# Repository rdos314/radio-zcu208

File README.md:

<h3>Source tree</h3>
vivado - Vivado Verilog source<br>
vitis - Vitis platform and control software<br>
linux - Peta-linux source<br>

<h3>PetaLinux build</h3>
Ubuntu 22.04.5 must be used to build PetaLinux. Link: https://releases.ubuntu.com/jammy/<br><br>

Create a user "ubuntu" since full paths are used in the source.

Install the required software modules before installing PetaLinux:<br>
sudo apt-get install iproute2 gawk python3 python build-essential gcc git make net-tools libncurses5-dev tftpd zlib1g-dev libssl-dev flex bison libselinux1 gnupg wget git-core diffstat chrpath socat xterm autoconf libtool tar unzip texinfo<br><br>

The PetaLinux installer can be downloaded here: https://www.xilinx.com/support/download/index.html/content/xilinx/en/downloadNav/embedded-design-tools.html<br>
Download the "PetaLinux installer" and the "ZCU208 BSP" to /home/ubuntu<br><br>

Install PetaLinux like this:<br>
chmod 755 ./petalinux-v2025.1-final-installer.run<br>
./petalinux-v2025.1-final-installer.run --dir /home/ubuntu/petalinux --platform "arm aarch64"<br>

Source PetaLinux before running commands:<br>
source /home/ubuntu/petalinux/settings.sh<br><br>

Create the project:<br>
mkdir radio-zcu208<br>
cd radio-zcu208<br><br>

petalinux-create -t project -s zcu208-v2025.1.bsp -n linux<br>
cd linux<br><br>

petalinux-config --get-hw-description ../platform/export/platform/hw/sdt<br><br>

Subsystem Hardware Settings -→ Memory settings -→ Set Memory size to 0x70000000<br>
Subsystem Hardware Settings -→ Ethernet settings -→ Disable obtain IP address automatically<br>
Subsystem Hardware Settings -→ Ethernet settings -→ Set Static IP address to 192.168.1.90<br>
Subsystem Hardware Settings -→ Ethernet settings -→ Set Static IP gateway to 192.168.1.1<br>
Image Packaging Configuration  -→  Set Root file system type to EXT4 (SD/eMMC/SATA/USB)<br>

Exit menuconfig and save configuration settings.<br><br>

petalinux-config -c rootfs.<br>

Filesystem Packages -→ console -→ network -→ OpenSSH -→ set openssh-sftp-server to enabled<br>
Filesystem Packages -→ misc -→ set tcf-agent to enabled<br>
Filesystem Packages -→ misc -→ set apache2 to enabled<br><br>

Exit menuconfig and save configuration settings.<br><br>

petalinux-build<br>
petalinux-package boot --uboot --force<br>
petalinux-build --sdk<br>
petalinux-package sysroot<br><br>

Copy linux/images/linux/b31.bin to project roo<br>
Copy linux/images/linux/system.dtb to project root<br>
Copy linux/images/linux/u-boot.elf to project root<br>
Copy linux/images/linux/sdk/sysroots/cortexa72-cotexa53-amd-linux/usr/include to project platform/usr/include<br>
Copy linux/images/linux/sdk/sysroots/cortexa72-cotexa53-amd-linux/usr/lib to project platform/usr/lib<br><br>

cp linux/images/linux/image.ub /media/ubuntu/boot<br>
cp linux/images/linux/boot.scr /media/ubuntu/boot<br>
sudo dd if=linux/images/linux/rootfs.ext4 of=/dev/sdb2<br><br>

<h3>Embedded Vitis</h3>

Embedded Vitis and Vivado can be installed either on Windows or on Linux. Link: https://www.xilinx.com/support/download/index.html/content/xilinx/en/downloadNav/vitis.html<br><br>

For Linux, download and install to /home/user/xilinx and then install the libs like this:<br>
cd /home/user/xilinx/2025.1/Vitis/scripts<br>
sudo ./installLibs.sh<br><br>

<h3>XRT and ZOCL</h3>

https://adaptivesupport.amd.com/s/article/1138667?language=en_US

<h3>Antennas and preamplifiers</h3>

Isolator: https://www.herostechnology.co.uk/pages/RF_Galvanic_Isolators.html                            3 MHz - 2.5 GHz<br>
LNA: https://www.pasternack.com/1.5-db-1.3-ghz-low-noise-amplifier-35-db-gain-sma-pe15a1054-p.aspx      10MHz - 1.3GHz, 35dB, 1.5 NF<br>
LNA: https://www.pasternack.com/1.7-db-550-mhz-low-noise-amplifier-29.7-db-gain-sma-pe15a1044-p.aspx    10MHz - 550 MHz, 30dB, 1.7 NF<br><br>

<h3>Example design</h3>

doc: https://docs.amd.com/r/en-US/ug1309-rf-data-converter-interface<br>
source: https://account.amd.com/en/forms/downloads/design-license-xef.html?filename=RF_Analyzer_2024_2.zip<br><br>

doc: https://www.xilinx.com/publications/products/board-kits/zcu208-dds-ila-2020p2.pdf<br>
source: https://account.amd.com/en/forms/downloads/design-license-xef.html?filename=ZCU208_dds_ila_2020p2.zip<br>

<h3>Important links</h3>
https://www.amd.com/en/products/adaptive-socs-and-fpgas/evaluation-boards/zcu208.html<br>
https://xilinx-wiki.atlassian.net/wiki/spaces/A/pages/18841823/Booting+via+Serial+ATA+SATA+on+ZCU102+Evaluation+Platform<br>
https://adaptivesupport.amd.com/s/article/000037805?language=en_US<br>
https://xilinx-wiki.atlassian.net/wiki/spaces/A/pages/18842475/PetaLinux+Yocto+Tips#PetaLinuxYoctoTips-HowtoAutoRunApplicationatStartup<br>
https://docs.amd.com/r/en-US/Vitis-Tutorials-Embedded-Software<br>
https://docs.amd.com/r/en-US/ug1209-embedded-design-tutorial/Tutorial-Design-Files<br>
https://numato.com/kb/styx-partitioning-sd-card-for-petalinux/<br>
https://adaptivesupport.amd.com/s/article/1192842?language=en_US<br>
https://github.com/Xilinx/embeddedsw/blob/master/XilinxProcessorIPLib/drivers/rfdc/examples/xrfdc_mts_example.c<br>
https://docs.amd.com/r/en-US/pg269-rf-data-converter/MTS-Sequencing<br>
https://docs.amd.com/r/en-US/ug835-vivado-tcl-commands/<br>
https://github.com/Xilinx/embeddedsw/tree/master/XilinxProcessorIPLib/drivers/board_common/src/rfclk<br>
https://layers.openembedded.org/layerindex/branch/master/layers/<br>
https://www.analog.com/en/products/adl5569.html<br>
https://ez.analog.com/rf/f/q-a/115814/adl5569-single-ended-input<br>

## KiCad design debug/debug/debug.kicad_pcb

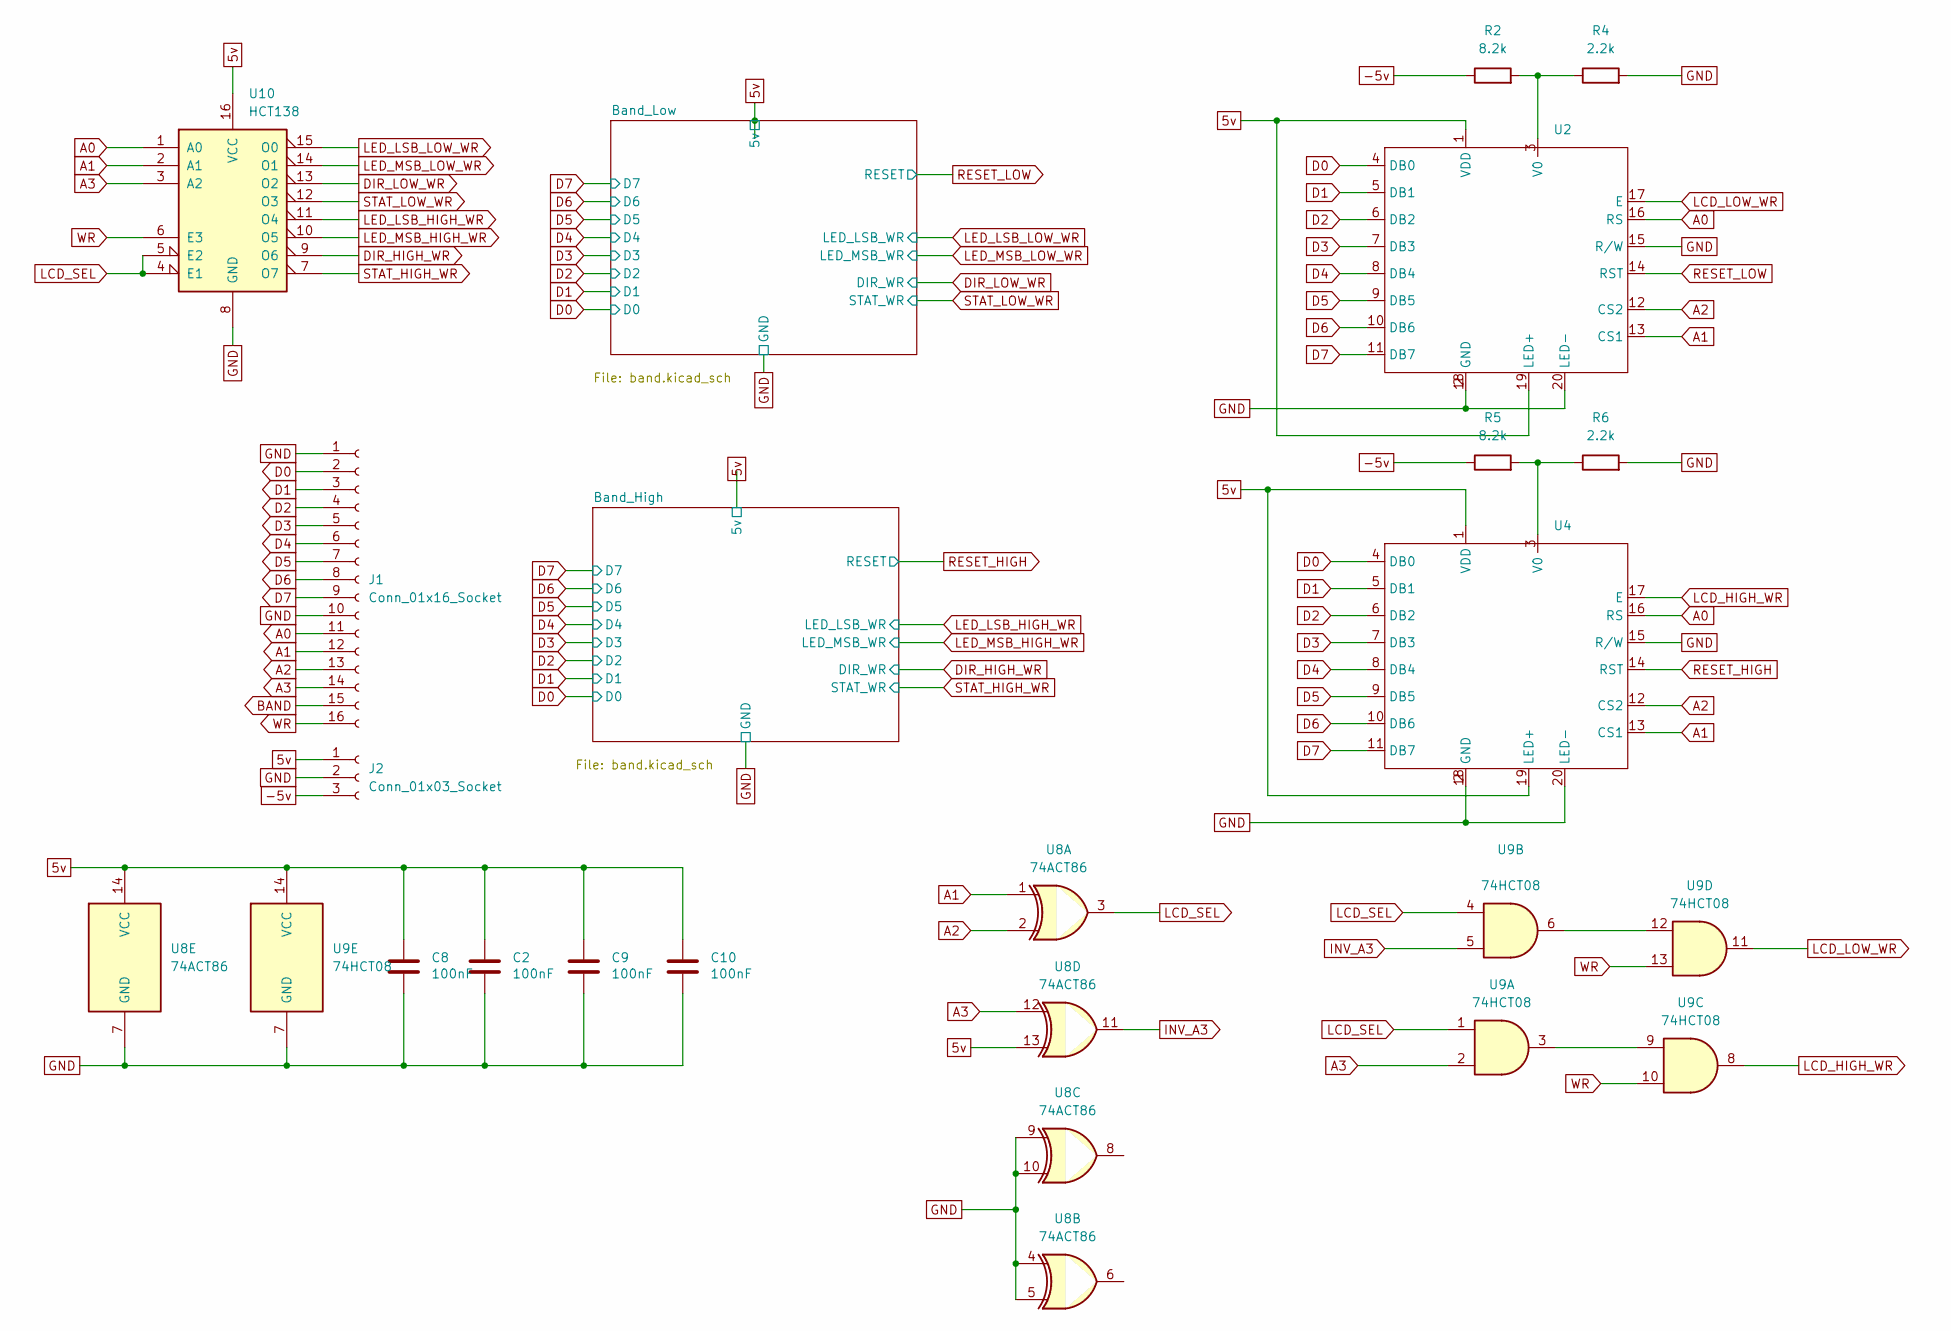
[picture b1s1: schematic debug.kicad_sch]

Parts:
C2, C8, C9, C10: 100nF; C_0805_2012Metric_Pad1.18x1.45mm_HandSolder
J1: Conn_01x16_Socket; PinSocket_1x16_P2.54mm_Vertical
J2: Conn_01x03_Socket; PinHeader_1x03_P2.54mm_Vertical
R2, R5: 8.2k; R_0805_2012Metric_Pad1.20x1.40mm_HandSolder
R4, R6: 2.2k; R_0805_2012Metric_Pad1.20x1.40mm_HandSolder
U2, U4: LCD
U8: 74ACT86; SOIC-14_3.9x8.7mm_P1.27mm
U9: 74HCT08; SOIC-14_3.9x8.7mm_P1.27mm
U10: HCT138; SOIC-16_3.9x9.9mm_P1.27mm

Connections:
5v: C2.1, C8.1, C9.1, C10.1, J2.1, U2.1 (VDD), U2.19 (LED+), U4.1 (VDD), U4.19 (LED+), U8.13, U8.14 (VCC), U9.14 (VCC), U10.16 (VCC); also elsewhere on the board
-5v: J2.3, R2.1, R5.1
A0: J1.11, U2.16 (RS), U4.16 (RS), U10.1 (A0)
A1: J1.12, U2.13 (CS1), U4.13 (CS1), U8.1, U10.2 (A1)
A2: J1.13, U2.12 (CS2), U4.12 (CS2), U8.2
A3: J1.14, U8.12, U9.2, U10.3 (A2)
BAND: J1.15
D0: J1.2, U2.4 (DB0), U4.4 (DB0); also elsewhere on the board
D1: J1.3, U2.5 (DB1), U4.5 (DB1); also elsewhere on the board
D2: J1.4, U2.6 (DB2), U4.6 (DB2); also elsewhere on the board
D3: J1.5, U2.7 (DB3), U4.7 (DB3); also elsewhere on the board
D4: J1.6, U2.8 (DB4), U4.8 (DB4); also elsewhere on the board
D5: J1.7, U2.9 (DB5), U4.9 (DB5); also elsewhere on the board
D6: J1.8, U2.10 (DB6), U4.10 (DB6); also elsewhere on the board
D7: J1.9, U2.11 (DB7), U4.11 (DB7); also elsewhere on the board
DIR_HIGH_WR: U10.9 (O6); also elsewhere on the board
DIR_LOW_WR: U10.13 (O2); also elsewhere on the board
GND: C2.2, C8.2, C9.2, C10.2, J1.1, J1.10, J2.2, R4.2, R6.2, U2.2 (GND), U2.15 (R/W), U2.18 (GND), U2.20 (LED-), U4.2 (GND), U4.15 (R/W), U4.18 (GND), U4.20 (LED-), U8.4, U8.5, U8.7 (GND), U8.9, U8.10, U9.7 (GND), U10.8 (GND); also elsewhere on the board
INV_A3: U8.11, U9.5
LCD_HIGH_WR: U4.17 (E), U9.8
LCD_LOW_WR: U2.17 (E), U9.11
LCD_SEL: U8.3, U9.1, U9.4, U10.4 (E1), U10.5 (E2)
LED_LSB_HIGH_WR: U10.11 (O4); also elsewhere on the board
LED_LSB_LOW_WR: U10.15 (O0); also elsewhere on the board
LED_MSB_HIGH_WR: U10.10 (O5); also elsewhere on the board
LED_MSB_LOW_WR: U10.14 (O1); also elsewhere on the board
unnamed: R2.2, R4.1, U2.3 (V0)
unnamed: R5.2, R6.1, U4.3 (V0)
unnamed: U9.3, U9.9
unnamed: U9.6, U9.12
RESET_HIGH: U4.14 (RST); also elsewhere on the board
RESET_LOW: U2.14 (RST); also elsewhere on the board
STAT_HIGH_WR: U10.7 (O7); also elsewhere on the board
STAT_LOW_WR: U10.12 (O3); also elsewhere on the board
WR: J1.16, U9.10, U9.13, U10.6 (E3)

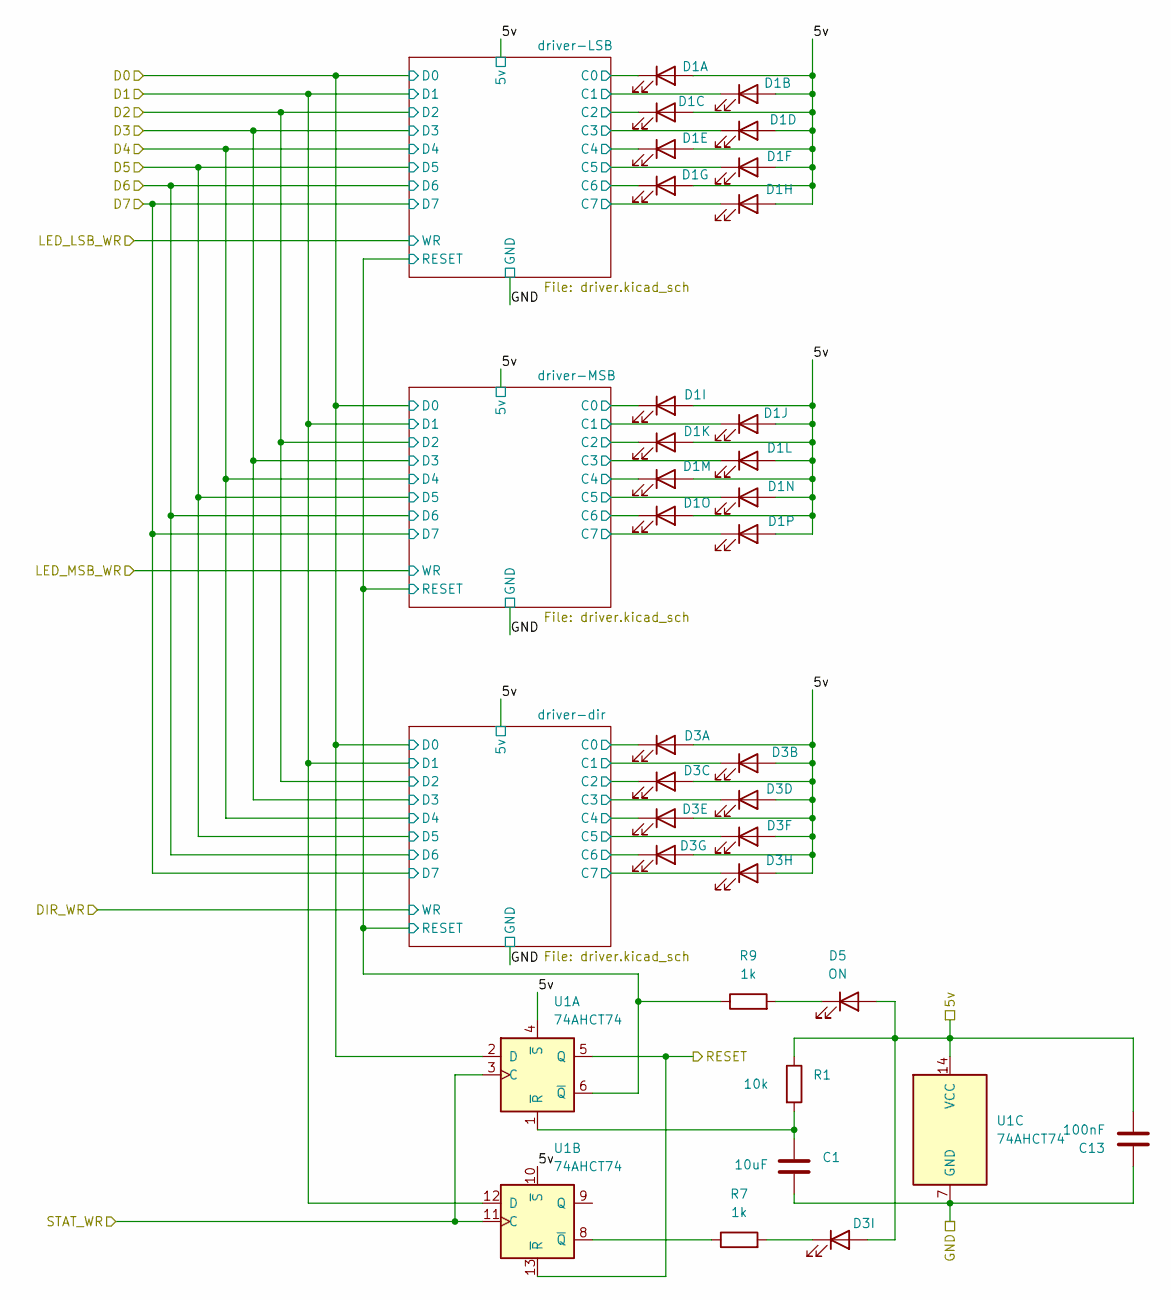
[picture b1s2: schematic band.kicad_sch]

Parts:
C1: 10uF; C_0805_2012Metric_Pad1.18x1.45mm_HandSolder
C13: 100nF; C_0805_2012Metric_Pad1.18x1.45mm_HandSolder
D1: LED-16x
D3: LED-dir
D5: ON; LED_D5.0mm
R1: 10k; R_0805_2012Metric_Pad1.20x1.40mm_HandSolder
R7, R9: 1k; R_0805_2012Metric_Pad1.20x1.40mm_HandSolder
U1: 74AHCT74; SOIC-14_3.9x8.7mm_P1.27mm

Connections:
5v: C13.2, D1.2 (A), D1.4 (A), D1.6 (A), D1.8 (A), D1.10 (A), D1.12 (A), D1.14 (A), D1.16 (A), D1.18 (A), D1.20 (A), D1.22 (A), D1.24 (A), D1.26 (A), D1.28 (A), D1.30 (A), D1.32 (A), D3.2 (A), D3.4 (A), D3.6 (A), D3.8 (A), D3.10 (A), D3.12 (A), D3.14 (A), D3.16 (A), D3.18 (A), D5.2 (A), R1.1, U1.4 (~S), U1.10 (~S), U1.14 (VCC); also elsewhere on the board
/Band_Low/driver-LSB/C0: D1.1 (K); also elsewhere on the board
/Band_Low/driver-LSB/C1: D1.3 (K); also elsewhere on the board
/Band_Low/driver-LSB/C2: D1.5 (K); also elsewhere on the board
/Band_Low/driver-LSB/C3: D1.7 (K); also elsewhere on the board
/Band_Low/driver-LSB/C4: D1.9 (K); also elsewhere on the board
/Band_Low/driver-LSB/C5: D1.11 (K); also elsewhere on the board
/Band_Low/driver-LSB/C6: D1.13 (K); also elsewhere on the board
/Band_Low/driver-LSB/C7: D1.15 (K); also elsewhere on the board
/Band_Low/driver-LSB/RESET: R9.1, U1.6 (~Q); also elsewhere on the board
/Band_Low/driver-MSB/C0: D1.17 (K); also elsewhere on the board
/Band_Low/driver-MSB/C1: D1.19 (K); also elsewhere on the board
/Band_Low/driver-MSB/C2: D1.21 (K); also elsewhere on the board
/Band_Low/driver-MSB/C3: D1.23 (K); also elsewhere on the board
/Band_Low/driver-MSB/C4: D1.25 (K); also elsewhere on the board
/Band_Low/driver-MSB/C5: D1.27 (K); also elsewhere on the board
/Band_Low/driver-MSB/C6: D1.29 (K); also elsewhere on the board
/Band_Low/driver-MSB/C7: D1.31 (K); also elsewhere on the board
/Band_Low/driver-dir/C0: D3.1 (K); also elsewhere on the board
/Band_Low/driver-dir/C1: D3.3 (K); also elsewhere on the board
/Band_Low/driver-dir/C2: D3.5 (K); also elsewhere on the board
/Band_Low/driver-dir/C3: D3.7 (K); also elsewhere on the board
/Band_Low/driver-dir/C4: D3.9 (K); also elsewhere on the board
/Band_Low/driver-dir/C5: D3.11 (K); also elsewhere on the board
/Band_Low/driver-dir/C6: D3.13 (K); also elsewhere on the board
/Band_Low/driver-dir/C7: D3.15 (K); also elsewhere on the board
D0: U1.2 (D); also elsewhere on the board
D1: U1.12 (D); also elsewhere on the board
GND: C1.2, C13.1, U1.7 (GND); also elsewhere on the board
unnamed: D3.17 (K), R7.2
unnamed: D5.1 (K), R9.2
unnamed: C1.1, R1.2, U1.1 (~R)
unnamed: R7.1, U1.8 (~Q)
RESET_LOW: U1.5 (Q), U1.13 (~R); also elsewhere on the board
STAT_LOW_WR: U1.3 (C), U1.11 (C); also elsewhere on the board

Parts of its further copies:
C3: 10uF; C_0805_2012Metric_Pad1.18x1.45mm_HandSolder
C15: 100nF; C_0805_2012Metric_Pad1.18x1.45mm_HandSolder
D2: LED-16x
D4: LED-dir
D6: ON; LED_D5.0mm
R3: 10k; R_0805_2012Metric_Pad1.20x1.40mm_HandSolder
R8, R10: 1k; R_0805_2012Metric_Pad1.20x1.40mm_HandSolder
U5: 74AHCT74; SOIC-14_3.9x8.7mm_P1.27mm

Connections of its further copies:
5v: C15.2, D2.2 (A), D2.4 (A), D2.6 (A), D2.8 (A), D2.10 (A), D2.12 (A), D2.14 (A), D2.16 (A), D2.18 (A), D2.20 (A), D2.22 (A), D2.24 (A), D2.26 (A), D2.28 (A), D2.30 (A), D2.32 (A), D4.2 (A), D4.4 (A), D4.6 (A), D4.8 (A), D4.10 (A), D4.12 (A), D4.14 (A), D4.16 (A), D4.18 (A), D6.2 (A), R3.1, U5.4 (~S), U5.10 (~S), U5.14 (VCC); also elsewhere on the board
/Band_High/driver-LSB/C0: D2.1 (K); also elsewhere on the board
/Band_High/driver-LSB/C1: D2.3 (K); also elsewhere on the board
/Band_High/driver-LSB/C2: D2.5 (K); also elsewhere on the board
/Band_High/driver-LSB/C3: D2.7 (K); also elsewhere on the board
/Band_High/driver-LSB/C4: D2.9 (K); also elsewhere on the board
/Band_High/driver-LSB/C5: D2.11 (K); also elsewhere on the board
/Band_High/driver-LSB/C6: D2.13 (K); also elsewhere on the board
/Band_High/driver-LSB/C7: D2.15 (K); also elsewhere on the board
/Band_High/driver-LSB/RESET: R10.1, U5.6 (~Q); also elsewhere on the board
/Band_High/driver-MSB/C0: D2.17 (K); also elsewhere on the board
/Band_High/driver-MSB/C1: D2.19 (K); also elsewhere on the board
/Band_High/driver-MSB/C2: D2.21 (K); also elsewhere on the board
/Band_High/driver-MSB/C3: D2.23 (K); also elsewhere on the board
/Band_High/driver-MSB/C4: D2.25 (K); also elsewhere on the board
/Band_High/driver-MSB/C5: D2.27 (K); also elsewhere on the board
/Band_High/driver-MSB/C6: D2.29 (K); also elsewhere on the board
/Band_High/driver-MSB/C7: D2.31 (K); also elsewhere on the board
/Band_High/driver-dir/C0: D4.1 (K); also elsewhere on the board
/Band_High/driver-dir/C1: D4.3 (K); also elsewhere on the board
/Band_High/driver-dir/C2: D4.5 (K); also elsewhere on the board
/Band_High/driver-dir/C3: D4.7 (K); also elsewhere on the board
/Band_High/driver-dir/C4: D4.9 (K); also elsewhere on the board
/Band_High/driver-dir/C5: D4.11 (K); also elsewhere on the board
/Band_High/driver-dir/C6: D4.13 (K); also elsewhere on the board
/Band_High/driver-dir/C7: D4.15 (K); also elsewhere on the board
D0: U5.2 (D); also elsewhere on the board
D1: U5.12 (D); also elsewhere on the board
GND: C3.2, C15.1, U5.7 (GND); also elsewhere on the board
unnamed: D4.17 (K), R8.2
unnamed: D6.1 (K), R10.2
unnamed: C3.1, R3.2, U5.1 (~R)
unnamed: R8.1, U5.8 (~Q)
RESET_HIGH: U5.5 (Q), U5.13 (~R); also elsewhere on the board
STAT_HIGH_WR: U5.3 (C), U5.11 (C); also elsewhere on the board

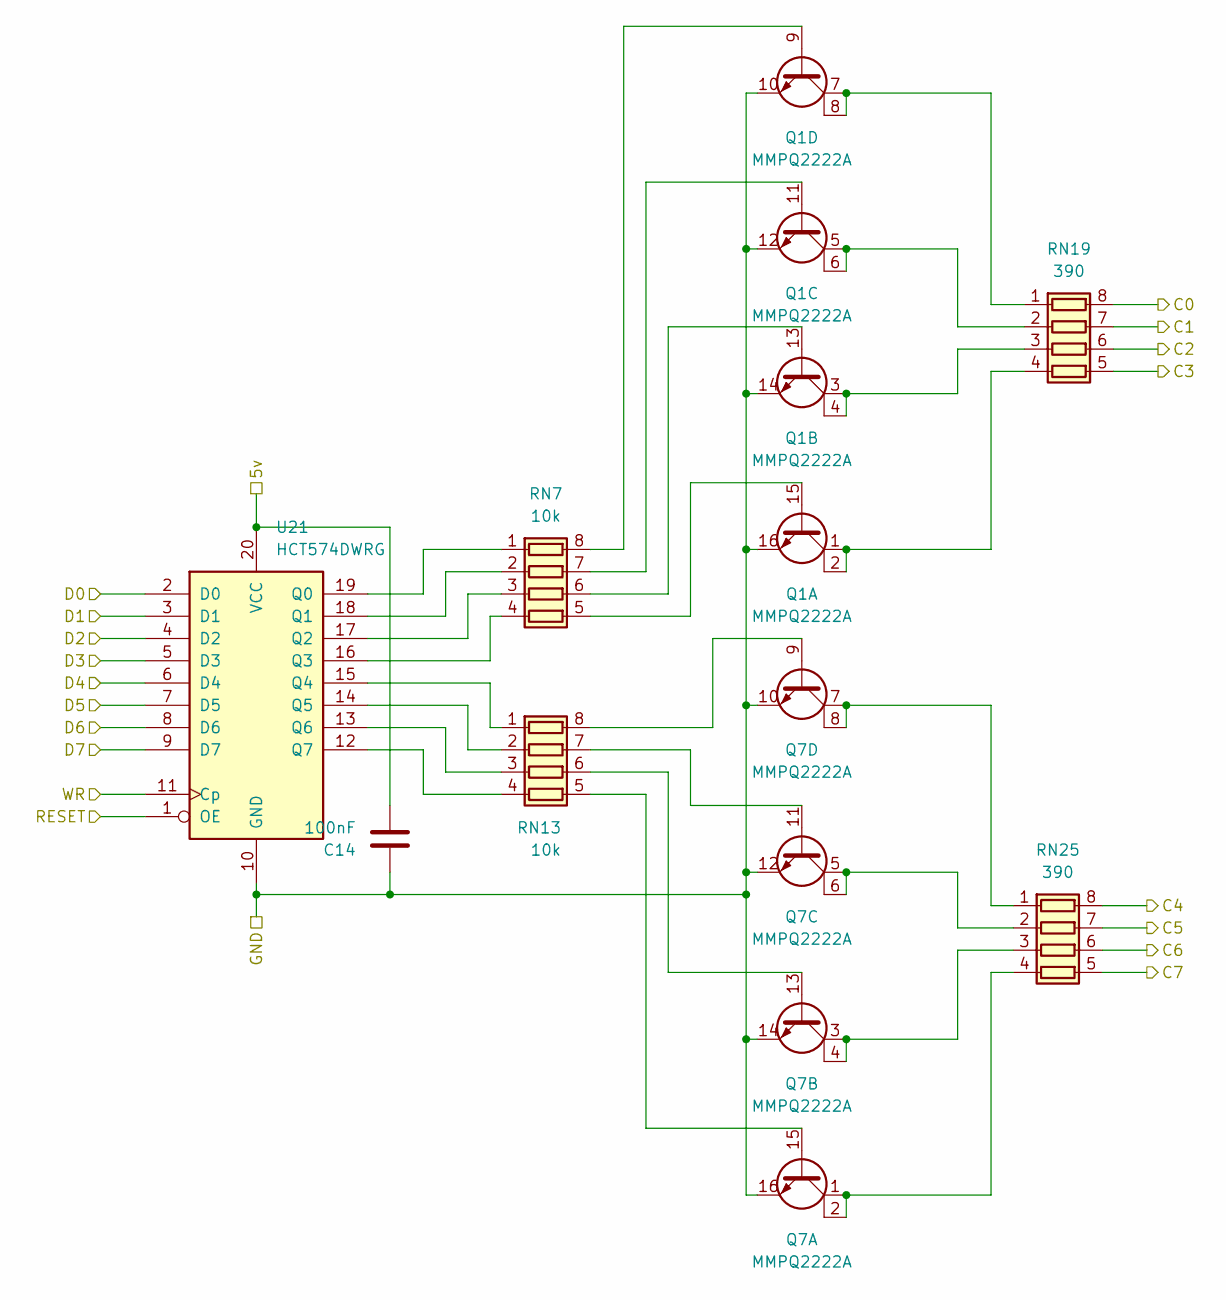
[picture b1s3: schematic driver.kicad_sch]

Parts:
C14: 100nF; C_0805_2012Metric_Pad1.18x1.45mm_HandSolder
Q1, Q7: MMPQ2222A; SO-16_3.9x9.9mm_P1.27mm
RN7, RN13: 10k; R_Array_Convex_4x0603
RN19, RN25: 390; R_Array_Convex_4x0603
U21: HCT574DWRG; SOIC-20W_7.5x12.8mm_P1.27mm

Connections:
5v: C14.2, U21.20 (VCC); also elsewhere on the board
/Band_Low/driver-LSB/C0: RN19.8 (R1.2); also elsewhere on the board
/Band_Low/driver-LSB/C1: RN19.7 (R2.2); also elsewhere on the board
/Band_Low/driver-LSB/C2: RN19.6 (R3.2); also elsewhere on the board
/Band_Low/driver-LSB/C3: RN19.5 (R4.2); also elsewhere on the board
/Band_Low/driver-LSB/C4: RN25.8 (R1.2); also elsewhere on the board
/Band_Low/driver-LSB/C5: RN25.7 (R2.2); also elsewhere on the board
/Band_Low/driver-LSB/C6: RN25.6 (R3.2); also elsewhere on the board
/Band_Low/driver-LSB/C7: RN25.5 (R4.2); also elsewhere on the board
/Band_Low/driver-LSB/RESET: U21.1 (OE); also elsewhere on the board
D0: U21.2 (D0); also elsewhere on the board
D1: U21.3 (D1); also elsewhere on the board
D2: U21.4 (D2); also elsewhere on the board
D3: U21.5 (D3); also elsewhere on the board
D4: U21.6 (D4); also elsewhere on the board
D5: U21.7 (D5); also elsewhere on the board
D6: U21.8 (D6); also elsewhere on the board
D7: U21.9 (D7); also elsewhere on the board
GND: C14.1, Q1.10 (E), Q1.12 (E), Q1.14 (E), Q1.16 (E), Q7.10 (E), Q7.12 (E), Q7.14 (E), Q7.16 (E), U21.10 (GND); also elsewhere on the board
LED_LSB_LOW_WR: U21.11 (Cp); also elsewhere on the board
unnamed: Q1.15 (B), RN7.5 (R4.2)
unnamed: Q1.13 (B), RN7.6 (R3.2)
unnamed: Q1.11 (B), RN7.7 (R2.2)
unnamed: Q1.9 (B), RN7.8 (R1.2)
unnamed: Q7.15 (B), RN13.5 (R4.2)
unnamed: Q7.13 (B), RN13.6 (R3.2)
unnamed: Q7.11 (B), RN13.7 (R2.2)
unnamed: Q7.9 (B), RN13.8 (R1.2)
unnamed: RN7.1 (R1.1), U21.19 (Q0)
unnamed: RN7.2 (R2.1), U21.18 (Q1)
unnamed: RN7.3 (R3.1), U21.17 (Q2)
unnamed: RN7.4 (R4.1), U21.16 (Q3)
unnamed: RN13.1 (R1.1), U21.15 (Q4)
unnamed: RN13.2 (R2.1), U21.14 (Q5)
unnamed: RN13.3 (R3.1), U21.13 (Q6)
unnamed: RN13.4 (R4.1), U21.12 (Q7)
unnamed: Q1.7 (C), Q1.8 (C), RN19.1 (R1.1)
unnamed: Q1.5 (C), Q1.6 (C), RN19.2 (R2.1)
unnamed: Q1.3 (C), Q1.4 (C), RN19.3 (R3.1)
unnamed: Q1.1 (C), Q1.2 (C), RN19.4 (R4.1)
unnamed: Q7.7 (C), Q7.8 (C), RN25.1 (R1.1)
unnamed: Q7.5 (C), Q7.6 (C), RN25.2 (R2.1)
unnamed: Q7.3 (C), Q7.4 (C), RN25.3 (R3.1)
unnamed: Q7.1 (C), Q7.2 (C), RN25.4 (R4.1)

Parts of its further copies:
C16, C17, C18, C19, C20: 100nF; C_0805_2012Metric_Pad1.18x1.45mm_HandSolder
Q2, Q3, Q4, Q5, Q6, Q8, Q9, Q10, Q11, Q12: MMPQ2222A; SO-16_3.9x9.9mm_P1.27mm
RN8, RN9, RN10, RN11, RN12, RN14, RN15, RN16, RN17, RN18: 10k; R_Array_Convex_4x0603
RN20, RN21, RN22, RN23, RN24, RN26, RN27, RN28, RN29, RN30: 390; R_Array_Convex_4x0603
U22, U23, U24, U25, U26: HCT574DWRG; SOIC-20W_7.5x12.8mm_P1.27mm

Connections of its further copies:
5v: C16.2, C17.2, C18.2, C19.2, C20.2, U22.20 (VCC), U23.20 (VCC), U24.20 (VCC), U25.20 (VCC), U26.20 (VCC); also elsewhere on the board
/Band_High/driver-LSB/C0: RN20.8 (R1.2); also elsewhere on the board
/Band_High/driver-LSB/C1: RN20.7 (R2.2); also elsewhere on the board
/Band_High/driver-LSB/C2: RN20.6 (R3.2); also elsewhere on the board
/Band_High/driver-LSB/C3: RN20.5 (R4.2); also elsewhere on the board
/Band_High/driver-LSB/C4: RN26.8 (R1.2); also elsewhere on the board
/Band_High/driver-LSB/C5: RN26.7 (R2.2); also elsewhere on the board
/Band_High/driver-LSB/C6: RN26.6 (R3.2); also elsewhere on the board
/Band_High/driver-LSB/C7: RN26.5 (R4.2); also elsewhere on the board
/Band_High/driver-LSB/RESET: U22.1 (OE), U24.1 (OE), U26.1 (OE); also elsewhere on the board
/Band_High/driver-MSB/C0: RN22.8 (R1.2); also elsewhere on the board
/Band_High/driver-MSB/C1: RN22.7 (R2.2); also elsewhere on the board
/Band_High/driver-MSB/C2: RN22.6 (R3.2); also elsewhere on the board
/Band_High/driver-MSB/C3: RN22.5 (R4.2); also elsewhere on the board
/Band_High/driver-MSB/C4: RN28.8 (R1.2); also elsewhere on the board
/Band_High/driver-MSB/C5: RN28.7 (R2.2); also elsewhere on the board
/Band_High/driver-MSB/C6: RN28.6 (R3.2); also elsewhere on the board
/Band_High/driver-MSB/C7: RN28.5 (R4.2); also elsewhere on the board
/Band_High/driver-dir/C0: RN24.8 (R1.2); also elsewhere on the board
/Band_High/driver-dir/C1: RN24.7 (R2.2); also elsewhere on the board
/Band_High/driver-dir/C2: RN24.6 (R3.2); also elsewhere on the board
/Band_High/driver-dir/C3: RN24.5 (R4.2); also elsewhere on the board
/Band_High/driver-dir/C4: RN30.8 (R1.2); also elsewhere on the board
/Band_High/driver-dir/C5: RN30.7 (R2.2); also elsewhere on the board
/Band_High/driver-dir/C6: RN30.6 (R3.2); also elsewhere on the board
/Band_High/driver-dir/C7: RN30.5 (R4.2); also elsewhere on the board
/Band_Low/driver-LSB/RESET: U23.1 (OE), U25.1 (OE); also elsewhere on the board
/Band_Low/driver-MSB/C0: RN21.8 (R1.2); also elsewhere on the board
/Band_Low/driver-MSB/C1: RN21.7 (R2.2); also elsewhere on the board
/Band_Low/driver-MSB/C2: RN21.6 (R3.2); also elsewhere on the board
/Band_Low/driver-MSB/C3: RN21.5 (R4.2); also elsewhere on the board
/Band_Low/driver-MSB/C4: RN27.8 (R1.2); also elsewhere on the board
/Band_Low/driver-MSB/C5: RN27.7 (R2.2); also elsewhere on the board
/Band_Low/driver-MSB/C6: RN27.6 (R3.2); also elsewhere on the board
/Band_Low/driver-MSB/C7: RN27.5 (R4.2); also elsewhere on the board
/Band_Low/driver-dir/C0: RN23.8 (R1.2); also elsewhere on the board
/Band_Low/driver-dir/C1: RN23.7 (R2.2); also elsewhere on the board
/Band_Low/driver-dir/C2: RN23.6 (R3.2); also elsewhere on the board
/Band_Low/driver-dir/C3: RN23.5 (R4.2); also elsewhere on the board
/Band_Low/driver-dir/C4: RN29.8 (R1.2); also elsewhere on the board
/Band_Low/driver-dir/C5: RN29.7 (R2.2); also elsewhere on the board
/Band_Low/driver-dir/C6: RN29.6 (R3.2); also elsewhere on the board
/Band_Low/driver-dir/C7: RN29.5 (R4.2); also elsewhere on the board
D0: U22.2 (D0), U23.2 (D0), U24.2 (D0), U25.2 (D0), U26.2 (D0); also elsewhere on the board
D1: U22.3 (D1), U23.3 (D1), U24.3 (D1), U25.3 (D1), U26.3 (D1); also elsewhere on the board
D2: U22.4 (D2), U23.4 (D2), U24.4 (D2), U25.4 (D2), U26.4 (D2); also elsewhere on the board
D3: U22.5 (D3), U23.5 (D3), U24.5 (D3), U25.5 (D3), U26.5 (D3); also elsewhere on the board
D4: U22.6 (D4), U23.6 (D4), U24.6 (D4), U25.6 (D4), U26.6 (D4); also elsewhere on the board
D5: U22.7 (D5), U23.7 (D5), U24.7 (D5), U25.7 (D5), U26.7 (D5); also elsewhere on the board
D6: U22.8 (D6), U23.8 (D6), U24.8 (D6), U25.8 (D6), U26.8 (D6); also elsewhere on the board
D7: U22.9 (D7), U23.9 (D7), U24.9 (D7), U25.9 (D7), U26.9 (D7); also elsewhere on the board
DIR_HIGH_WR: U26.11 (Cp); also elsewhere on the board
DIR_LOW_WR: U25.11 (Cp); also elsewhere on the board
GND: C16.1, C17.1, C18.1, C19.1, C20.1, Q2.10 (E), Q2.12 (E), Q2.14 (E), Q2.16 (E), Q3.10 (E), Q3.12 (E), Q3.14 (E), Q3.16 (E), Q4.10 (E), Q4.12 (E), Q4.14 (E), Q4.16 (E), Q5.10 (E), Q5.12 (E), Q5.14 (E), Q5.16 (E), Q6.10 (E), Q6.12 (E), Q6.14 (E), Q6.16 (E), Q8.10 (E), Q8.12 (E), Q8.14 (E), Q8.16 (E), Q9.10 (E), Q9.12 (E), Q9.14 (E), Q9.16 (E), Q10.10 (E), Q10.12 (E), Q10.14 (E), Q10.16 (E), Q11.10 (E), Q11.12 (E), Q11.14 (E), Q11.16 (E), Q12.10 (E), Q12.12 (E), Q12.14 (E), Q12.16 (E), U22.10 (GND), U23.10 (GND), U24.10 (GND), U25.10 (GND), U26.10 (GND); also elsewhere on the board
LED_LSB_HIGH_WR: U22.11 (Cp); also elsewhere on the board
LED_MSB_HIGH_WR: U24.11 (Cp); also elsewhere on the board
LED_MSB_LOW_WR: U23.11 (Cp); also elsewhere on the board
unnamed: Q2.15 (B), RN8.5 (R4.2)
unnamed: Q2.13 (B), RN8.6 (R3.2)
unnamed: Q2.11 (B), RN8.7 (R2.2)
unnamed: Q2.9 (B), RN8.8 (R1.2)
unnamed: Q3.15 (B), RN9.5 (R4.2)
unnamed: Q3.13 (B), RN9.6 (R3.2)
unnamed: Q3.11 (B), RN9.7 (R2.2)
unnamed: Q3.9 (B), RN9.8 (R1.2)
unnamed: Q4.15 (B), RN10.5 (R4.2)
unnamed: Q4.13 (B), RN10.6 (R3.2)
unnamed: Q4.11 (B), RN10.7 (R2.2)
unnamed: Q4.9 (B), RN10.8 (R1.2)
unnamed: Q5.15 (B), RN11.5 (R4.2)
unnamed: Q5.13 (B), RN11.6 (R3.2)
unnamed: Q5.11 (B), RN11.7 (R2.2)
unnamed: Q5.9 (B), RN11.8 (R1.2)
unnamed: Q6.15 (B), RN12.5 (R4.2)
unnamed: Q6.13 (B), RN12.6 (R3.2)
unnamed: Q6.11 (B), RN12.7 (R2.2)
unnamed: Q6.9 (B), RN12.8 (R1.2)
unnamed: Q8.15 (B), RN14.5 (R4.2)
unnamed: Q8.13 (B), RN14.6 (R3.2)
unnamed: Q8.11 (B), RN14.7 (R2.2)
unnamed: Q8.9 (B), RN14.8 (R1.2)
unnamed: Q9.15 (B), RN15.5 (R4.2)
unnamed: Q9.13 (B), RN15.6 (R3.2)
unnamed: Q9.11 (B), RN15.7 (R2.2)
unnamed: Q9.9 (B), RN15.8 (R1.2)
unnamed: Q10.15 (B), RN16.5 (R4.2)
unnamed: Q10.13 (B), RN16.6 (R3.2)
unnamed: Q10.11 (B), RN16.7 (R2.2)
unnamed: Q10.9 (B), RN16.8 (R1.2)
unnamed: Q11.15 (B), RN17.5 (R4.2)
unnamed: Q11.13 (B), RN17.6 (R3.2)
unnamed: Q11.11 (B), RN17.7 (R2.2)
unnamed: Q11.9 (B), RN17.8 (R1.2)
unnamed: Q12.15 (B), RN18.5 (R4.2)
unnamed: Q12.13 (B), RN18.6 (R3.2)
unnamed: Q12.11 (B), RN18.7 (R2.2)
unnamed: Q12.9 (B), RN18.8 (R1.2)
unnamed: RN8.1 (R1.1), U22.19 (Q0)
unnamed: RN8.2 (R2.1), U22.18 (Q1)
unnamed: RN8.3 (R3.1), U22.17 (Q2)
unnamed: RN8.4 (R4.1), U22.16 (Q3)
unnamed: RN9.1 (R1.1), U23.19 (Q0)
unnamed: RN9.2 (R2.1), U23.18 (Q1)
unnamed: RN9.3 (R3.1), U23.17 (Q2)
unnamed: RN9.4 (R4.1), U23.16 (Q3)
unnamed: RN10.1 (R1.1), U24.19 (Q0)
unnamed: RN10.2 (R2.1), U24.18 (Q1)
unnamed: RN10.3 (R3.1), U24.17 (Q2)
unnamed: RN10.4 (R4.1), U24.16 (Q3)
unnamed: RN11.1 (R1.1), U25.19 (Q0)
unnamed: RN11.2 (R2.1), U25.18 (Q1)
unnamed: RN11.3 (R3.1), U25.17 (Q2)
unnamed: RN11.4 (R4.1), U25.16 (Q3)
unnamed: RN12.1 (R1.1), U26.19 (Q0)
unnamed: RN12.2 (R2.1), U26.18 (Q1)
unnamed: RN12.3 (R3.1), U26.17 (Q2)
unnamed: RN12.4 (R4.1), U26.16 (Q3)
unnamed: RN14.1 (R1.1), U22.15 (Q4)
unnamed: RN14.2 (R2.1), U22.14 (Q5)
unnamed: RN14.3 (R3.1), U22.13 (Q6)
unnamed: RN14.4 (R4.1), U22.12 (Q7)
unnamed: RN15.1 (R1.1), U23.15 (Q4)
unnamed: RN15.2 (R2.1), U23.14 (Q5)
unnamed: RN15.3 (R3.1), U23.13 (Q6)
unnamed: RN15.4 (R4.1), U23.12 (Q7)
unnamed: RN16.1 (R1.1), U24.15 (Q4)
unnamed: RN16.2 (R2.1), U24.14 (Q5)
unnamed: RN16.3 (R3.1), U24.13 (Q6)
unnamed: RN16.4 (R4.1), U24.12 (Q7)
unnamed: RN17.1 (R1.1), U25.15 (Q4)
unnamed: RN17.2 (R2.1), U25.14 (Q5)
unnamed: RN17.3 (R3.1), U25.13 (Q6)
unnamed: RN17.4 (R4.1), U25.12 (Q7)
unnamed: RN18.1 (R1.1), U26.15 (Q4)
unnamed: RN18.2 (R2.1), U26.14 (Q5)
unnamed: RN18.3 (R3.1), U26.13 (Q6)
unnamed: RN18.4 (R4.1), U26.12 (Q7)
unnamed: Q2.7 (C), Q2.8 (C), RN20.1 (R1.1)
unnamed: Q2.5 (C), Q2.6 (C), RN20.2 (R2.1)
unnamed: Q2.3 (C), Q2.4 (C), RN20.3 (R3.1)
unnamed: Q2.1 (C), Q2.2 (C), RN20.4 (R4.1)
unnamed: Q3.7 (C), Q3.8 (C), RN21.1 (R1.1)
unnamed: Q3.5 (C), Q3.6 (C), RN21.2 (R2.1)
unnamed: Q3.3 (C), Q3.4 (C), RN21.3 (R3.1)
unnamed: Q3.1 (C), Q3.2 (C), RN21.4 (R4.1)
unnamed: Q4.7 (C), Q4.8 (C), RN22.1 (R1.1)
unnamed: Q4.5 (C), Q4.6 (C), RN22.2 (R2.1)
unnamed: Q4.3 (C), Q4.4 (C), RN22.3 (R3.1)
unnamed: Q4.1 (C), Q4.2 (C), RN22.4 (R4.1)
unnamed: Q5.7 (C), Q5.8 (C), RN23.1 (R1.1)
unnamed: Q5.5 (C), Q5.6 (C), RN23.2 (R2.1)
unnamed: Q5.3 (C), Q5.4 (C), RN23.3 (R3.1)
unnamed: Q5.1 (C), Q5.2 (C), RN23.4 (R4.1)
unnamed: Q6.7 (C), Q6.8 (C), RN24.1 (R1.1)
unnamed: Q6.5 (C), Q6.6 (C), RN24.2 (R2.1)
unnamed: Q6.3 (C), Q6.4 (C), RN24.3 (R3.1)
unnamed: Q6.1 (C), Q6.2 (C), RN24.4 (R4.1)
unnamed: Q8.7 (C), Q8.8 (C), RN26.1 (R1.1)
unnamed: Q8.5 (C), Q8.6 (C), RN26.2 (R2.1)
unnamed: Q8.3 (C), Q8.4 (C), RN26.3 (R3.1)
unnamed: Q8.1 (C), Q8.2 (C), RN26.4 (R4.1)
unnamed: Q9.7 (C), Q9.8 (C), RN27.1 (R1.1)
unnamed: Q9.5 (C), Q9.6 (C), RN27.2 (R2.1)
unnamed: Q9.3 (C), Q9.4 (C), RN27.3 (R3.1)
unnamed: Q9.1 (C), Q9.2 (C), RN27.4 (R4.1)
unnamed: Q10.7 (C), Q10.8 (C), RN28.1 (R1.1)
unnamed: Q10.5 (C), Q10.6 (C), RN28.2 (R2.1)
unnamed: Q10.3 (C), Q10.4 (C), RN28.3 (R3.1)
unnamed: Q10.1 (C), Q10.2 (C), RN28.4 (R4.1)
unnamed: Q11.7 (C), Q11.8 (C), RN29.1 (R1.1)
unnamed: Q11.5 (C), Q11.6 (C), RN29.2 (R2.1)
unnamed: Q11.3 (C), Q11.4 (C), RN29.3 (R3.1)
unnamed: Q11.1 (C), Q11.2 (C), RN29.4 (R4.1)
unnamed: Q12.7 (C), Q12.8 (C), RN30.1 (R1.1)
unnamed: Q12.5 (C), Q12.6 (C), RN30.2 (R2.1)
unnamed: Q12.3 (C), Q12.4 (C), RN30.3 (R3.1)
unnamed: Q12.1 (C), Q12.2 (C), RN30.4 (R4.1)

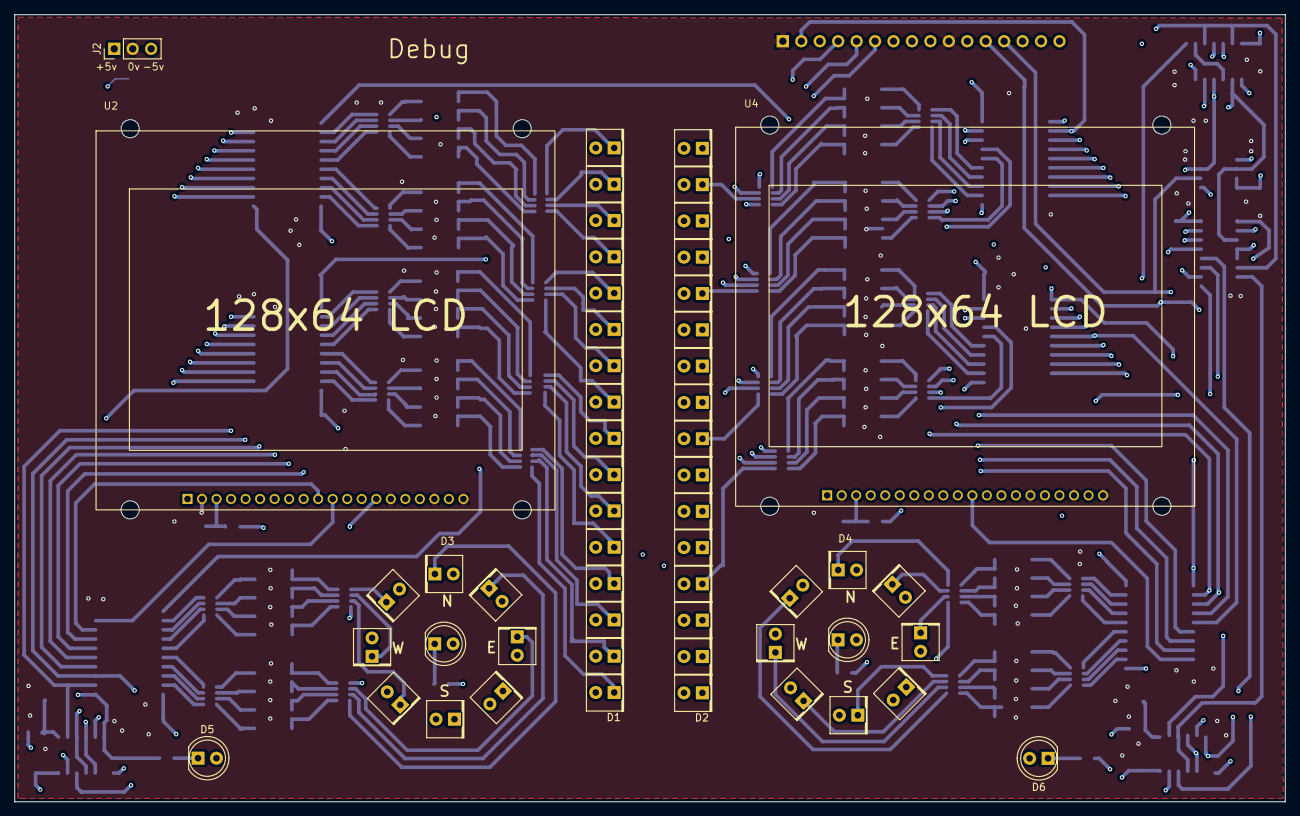
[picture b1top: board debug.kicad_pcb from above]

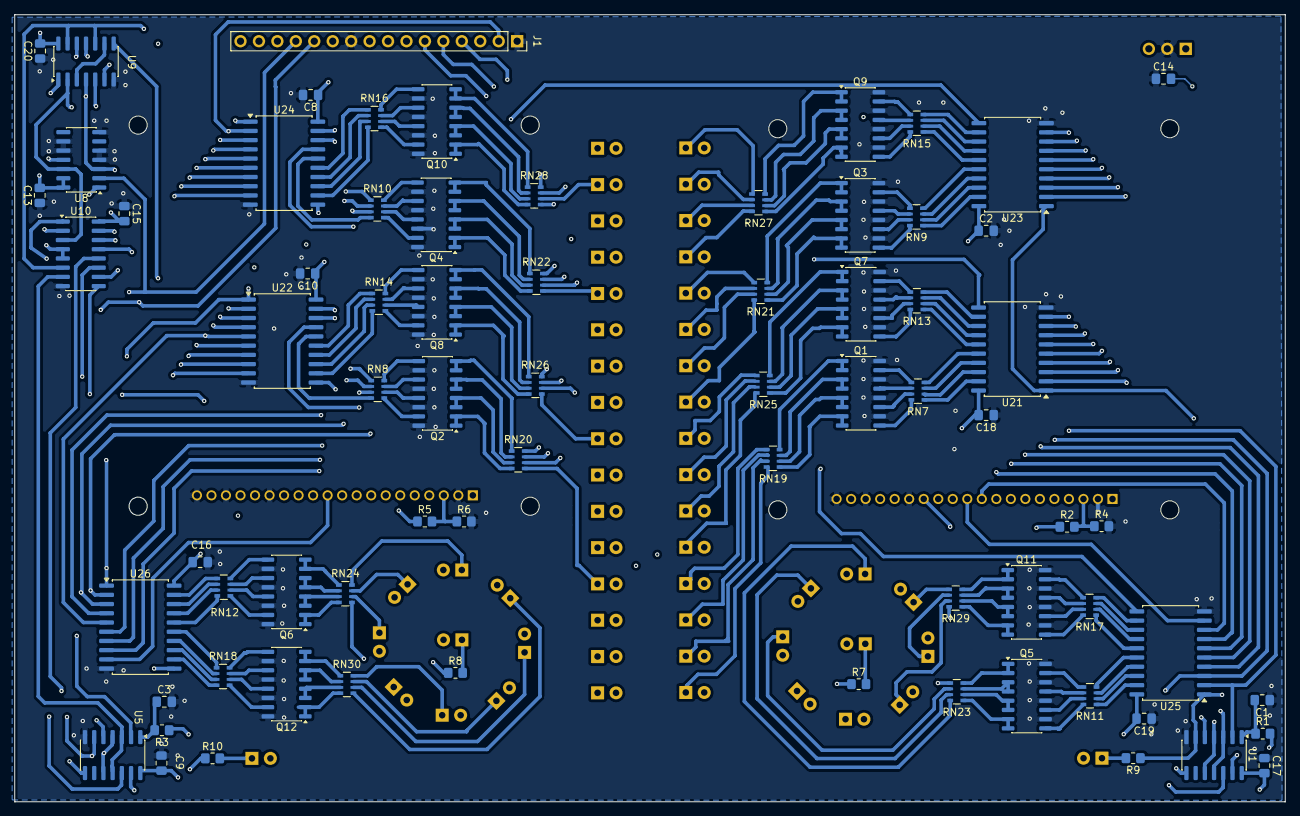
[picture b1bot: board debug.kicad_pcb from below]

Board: 4 copper layers, 175.0 x 108.4 mm, 81 parts (72 on the bottom side), 236 nets.
